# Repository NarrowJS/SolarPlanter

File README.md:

# SolarPlanter

A solar powered smart planter with built in soil moisture level monitoring.

## Key Features

- **ESP32-C3** microcontroller with WiFi + BLE Support
- **650 MAH** LiPo for backup power
- Built in **RGB LEDS** for notifications
- **Online logging** and monitoring via ESPHome
- **Motion sensor** to provide relevant notifications
- **ADC** to monitor battery voltage levels

## Why?

Keeping track of your plant's mositure, knowing when to water it, and also remembering to water it can be a challenging task, especially if you have more than one plant. Wanting a solution that was discrete and did not need me to ever charge the battery led me to make SolarPlanter.

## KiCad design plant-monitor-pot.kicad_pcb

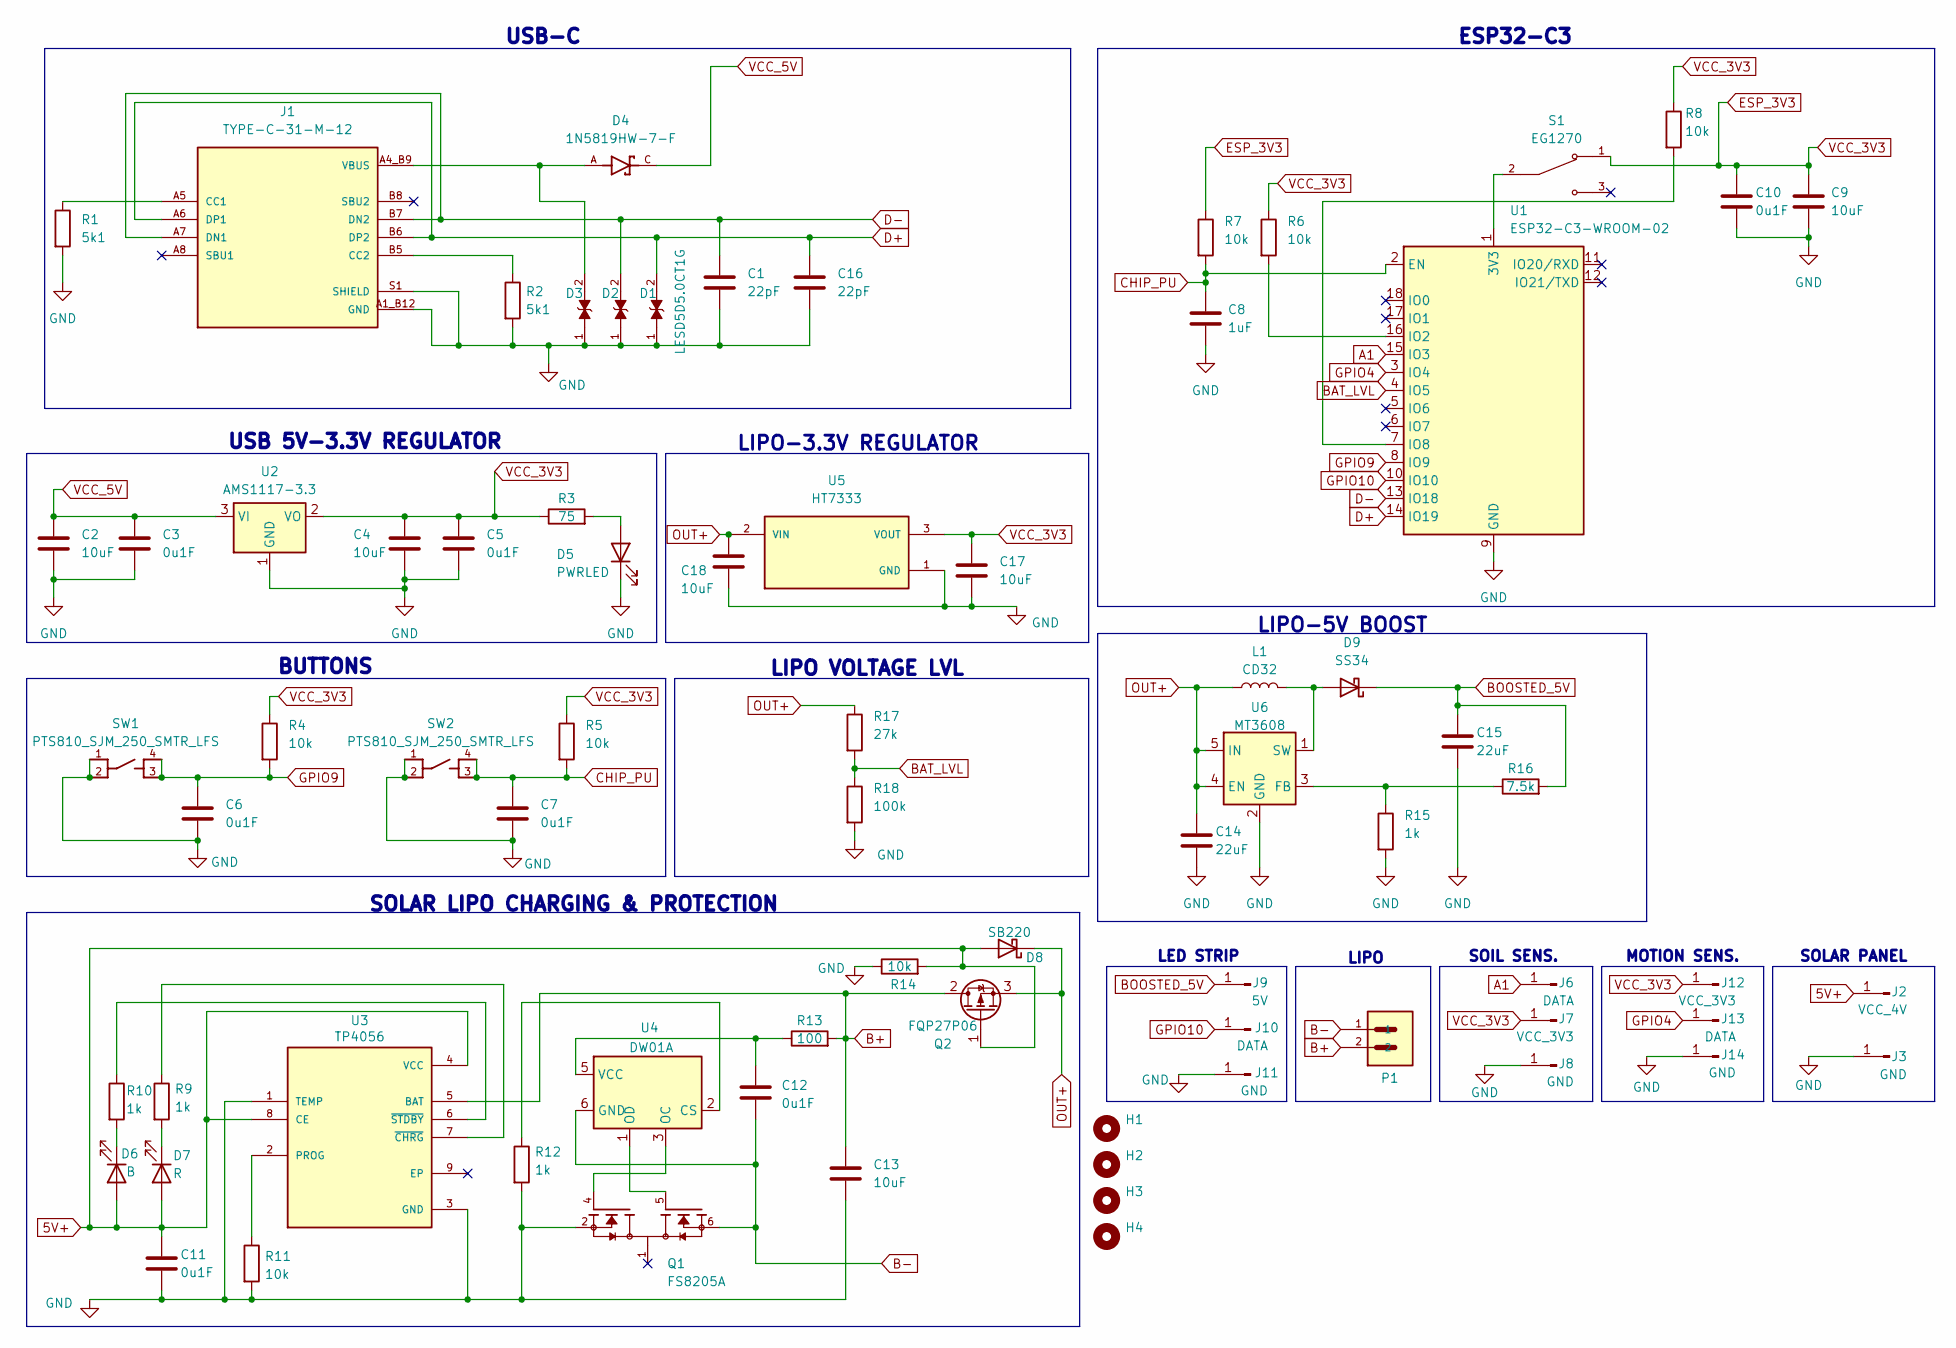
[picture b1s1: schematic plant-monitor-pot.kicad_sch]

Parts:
C1, C16: 22pF; C_0805_2012Metric
C2, C4, C9, C13, C17, C18: 10uF; C_0805_2012Metric
C3, C5, C6, C7, C10, C11, C12: 0u1F; C_0805_2012Metric
C8: 1uF; C_0805_2012Metric
C14, C15: 22uF; C_0805_2012Metric
D1, D2, D3: LESD5D5.0CT1G; TVS_LESD5D5.0CT1G; PARTREV O
D4: 1N5819HW-7-F; SOD3715X145N; PARTREV 18-2
D5: PWRLED; LED_0402_1005Metric
D6: B; LED_0402_1005Metric
D7: R; LED_0402_1005Metric
D8: SB220; D_0402_1005Metric
D9: SS34; D_SMA
H1, H2, H3, H4: MountingHole; MountingHole_2.2mm_M2
J1: TYPE-C-31-M-12; HRO_TYPE-C-31-M-12; PARTREV 2020.12.08
J2: VCC_4V; SolderWirePad_1x01_SMD_1x2mm
J3, J8, J11, J14: GND; SolderWirePad_1x01_SMD_1x2mm
J6, J10, J13: DATA; SolderWirePad_1x01_SMD_1x2mm
J7, J12: VCC_3V3; SolderWirePad_1x01_SMD_1x2mm
J9: 5V; SolderWirePad_1x01_SMD_1x2mm
L1: CD32; D_SMP_DO-220AA
P1: S2B-PH-SM4-TB; JST_S2B-PH-SM4-TB
Q1: FS8205A; SOP65P640X120-8N; PARTREV 1.7
Q2: FQP27P06; TO-220-3_Vertical
R1, R2: 5k1; R_0805_2012Metric
R3: 75; R_0805_2012Metric
R4, R5, R6, R7, R8, R11, R14: 10k; R_0805_2012Metric
R9, R10, R12, R15: 1k; R_0805_2012Metric
R13: 100; R_0805_2012Metric
R16: 7.5k; R_0805_2012Metric
R17: 27k; R_0805_2012Metric
R18: 100k; R_0805_2012Metric
S1: EG1270; SW_EG1270
SW1, SW2: PTS810_SJM_250_SMTR_LFS; SW_PTS810_SJM_250_SMTR_LFS
U1: ESP32-C3-WROOM-02
U2: AMS1117-3.3; SOT-223-3_TabPin2
U3: TP4056; SOP127P600X175-9N
U4: DW01A; SOT-23-6
U5: HT7333; IC_HT7333; PARTREV 1.80
U6: MT3608; SOT-23-6

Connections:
5V+: C11.1, D6.2 (A), D7.2 (A), D8.2 (A), J2.1, Q2.1 (G), R14.2, U3.4 (VCC), U3.8 (CE); also elsewhere on the board
A1: J6.1, U1.15 (IO3)
B+: C13.1, P1.2, Q2.2 (D), R13.2, U3.5 (BAT)
B-: C12.2, P1.1, Q1.6, Q1.7, U4.6 (GND)
BAT_LVL: R17.2, R18.1, U1.4 (IO5)
BOOSTED_5V: C15.1, D9.1 (K), J9.1, R16.2
CHIP_PU: C7.1, C8.1, R5.2, R7.2, SW2.3, SW2.4, U1.2 (EN)
D+: C16.1, D1.2, J1.A6 (DP1), J1.B6 (DP2), U1.14 (IO19)
D-: C1.1, D2.2, J1.A7 (DN1), J1.B7 (DN2), U1.13 (IO18)
ESP_3V3: C4.1, C5.1, C9.1, C10.1, C17.1, J7.1, J12.1, R3.1, R4.1, R5.1, R6.1, R7.1, R8.1, S1.1, U2.2 (VO), U5.3 (VOUT)
GND: C1.2, C2.2, C3.2, C4.2, C5.2, C6.2, C7.2, C8.2, C9.2, C10.2, C11.2, C13.2, C14.2, C15.2, C16.2, C17.2, C18.2, D1.1, D2.1, D3.1, D5.1 (K), J1.A1_B12 (GND), J1.B1_A12 (GND), J1.S1 (SHIELD), J1.S2 (SHIELD), J1.S3 (SHIELD), J1.S4 (SHIELD), J3.1, J8.1, J11.1, J14.1, Q1.2, Q1.3, R1.2, R2.2, R11.2, R12.2, R14.1, R15.2, R18.2, SW1.1, SW1.2, SW2.1, SW2.2, U1.9 (GND), U1.19 (GND), U2.1 (GND), U3.1 (TEMP), U3.3 (GND), U5.1 (GND), U6.2 (GND); also elsewhere on the board
GPIO4: J13.1, U1.3 (IO4)
GPIO9: C6.1, R4.2, SW1.3, SW1.4, U1.8 (IO9)
GPIO10: J10.1, U1.10 (IO10)
unnamed 14: D5.2 (A), R3.2; also elsewhere on the board
unnamed: D6.1 (K), R10.2
unnamed: D7.1 (K), R9.2
unnamed: D9.2 (A), L1.2, U6.1 (SW)
unnamed: J1.A5 (CC1), R1.1
unnamed: J1.B5 (CC2), R2.1
unnamed: S1.2, U1.1 (3V3)
unnamed: R6.2, U1.16 (IO2)
unnamed: R8.2, U1.7 (IO8)
unnamed: R11.1, U3.2 (PROG)
unnamed: R9.1, U3.7 (~CHRG)
unnamed: R10.1, U3.6 (~STDBY)
unnamed: R12.1, U4.2 (CS)
unnamed: Q1.4, U4.3 (OC)
unnamed: Q1.5, U4.1 (OD)
unnamed: C12.1, R13.1, U4.5 (VCC)
unnamed: R15.1, R16.1, U6.3 (FB)
OUT+: C14.1, C18.1, D8.1 (K), L1.1, Q2.3 (S), R17.1, U5.2 (VIN), U6.4 (EN), U6.5 (IN); also elsewhere on the board
VBUS: D3.2, D4.A, J1.A4_B9 (VBUS), J1.B4_A9 (VBUS)
VCC_5V: C2.1, C3.1, D4.C, U2.3 (VI)

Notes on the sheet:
BUTTONS
SOLAR PANEL
LIPO
SOIL SENS.
LED STRIP
ESP32-C3
USB-C
MOTION SENS.
USB 5V-3.3V REGULATOR
LIPO-5V BOOST
SOLAR LIPO CHARGING & PROTECTION
LIPO VOLTAGE LVL
LIPO-3.3V REGULATOR

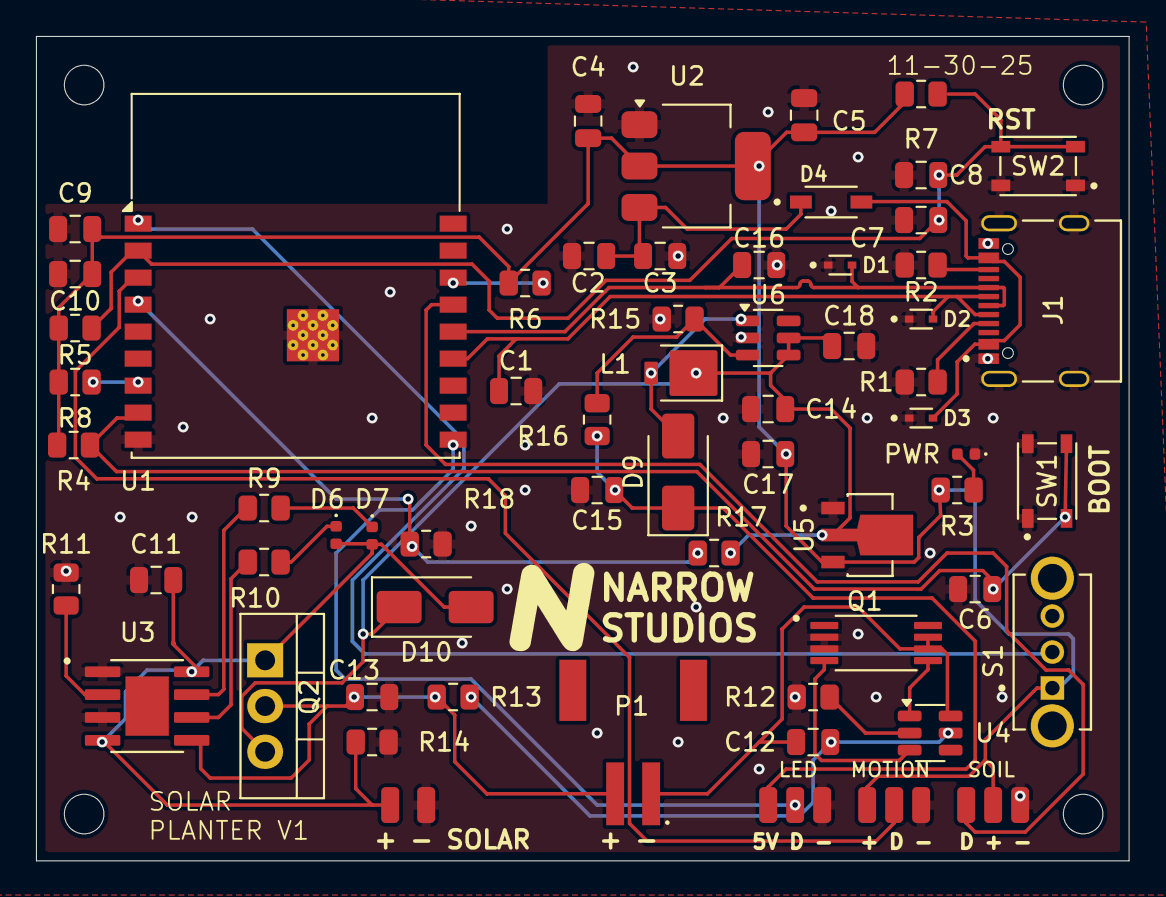
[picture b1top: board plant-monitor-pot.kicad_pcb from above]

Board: 2 copper layers, 60.7 x 45.8 mm, 75 parts (0 on the bottom side), 34 nets.

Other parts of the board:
D10: SS24; D_SMA
PWR: PWRLED; LED_0402_1005Metric
e: LOGO; ns-logo

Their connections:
5V+: D10.2 (A); also elsewhere on the board
GND: PWR.1 (K); also elsewhere on the board
unnamed 14: PWR.2 (A); also elsewhere on the board
OUT+: D10.1 (K); also elsewhere on the board

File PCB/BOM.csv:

"Id";"Designator";"Footprint";"Quantity";"Designation";"Supplier and ref";
1;"R9,R15,R10,R12";"R_0805_2012Metric";4;"1k";;;
2;"J3,J14,J8,J11";"SolderWirePad_1x01_SMD_1x2mm";4;"GND";;;
3;"J7,J12";"SolderWirePad_1x01_SMD_1x2mm";2;"VCC_3V3";;;
4;"R1,R2";"R_0805_2012Metric";2;"5k1";;;
5;"L1";"D_SMP_DO-220AA";1;"CD32";;;
6;"U2";"SOT-223-3_TabPin2";1;"AMS1117-3.3";;;
7;"U6";"SOT-23-6";1;"MT3608";;;
8;"D4";"SOD3715X145N";1;"1N5819HW-7-F";;;
9;"C18,C17,C13,C4,C2,C9";"C_0805_2012Metric";6;"10uF";;;
10;"J10,J6,J13";"SolderWirePad_1x01_SMD_1x2mm";3;"DATA";;;
11;"S1";"SW_EG1270";1;"EG1270";;;
12;"P1";"JST_S2B-PH-SM4-TB";1;"S2B-PH-SM4-TB";;;
13;"R3";"R_0805_2012Metric";1;"75";;;
14;"Q2";"TO-220-3_Vertical";1;"FQP27P06";;;
15;"J1";"HRO_TYPE-C-31-M-12";1;"TYPE-C-31-M-12";;;
16;"R11,R6,R7,R5,R8,R4,R14";"R_0805_2012Metric";7;"10k";;;
17;"SW2,SW1";"SW_PTS810_SJM_250_SMTR_LFS";2;"PTS810_SJM_250_SMTR_LFS";;;
18;"C15,C14";"C_0805_2012Metric";2;"22uF";;;
19;"C10,C7,C3,C5,C11,C12,C6";"C_0805_2012Metric";7;"0u1F";;;
20;"U4";"SOT-23-6";1;"DW01A";;;
21;"C16,C1";"C_0805_2012Metric";2;"22pF";;;
22;"U1";"ESP32-C3-WROOM-02";1;"ESP32-C3-WROOM-02";;;
23;"R18";"R_0805_2012Metric";1;"100k";;;
24;"R17";"R_0805_2012Metric";1;"27k";;;
25;"D6";"LED_0402_1005Metric";1;"B";;;
26;"R16";"R_0805_2012Metric";1;"7.5k";;;
27;"J9";"SolderWirePad_1x01_SMD_1x2mm";1;"5V";;;
28;"D8";"D_0402_1005Metric";1;"SB220";;;
29;"Q1";"SOP65P640X120-8N";1;"FS8205A";;;
30;"D7";"LED_0402_1005Metric";1;"R";;;
31;"U3";"SOP127P600X175-9N";1;"TP4056";;;
32;"C8";"C_0805_2012Metric";1;"1uF";;;
33;"D9";"D_SMA";1;"SS34";;;
34;"D2,D3,D1";"TVS_LESD5D5.0CT1G";3;"LESD5D5.0CT1G";;;
35;"U5";"IC_HT7333";1;"HT7333";;;
36;"R13";"R_0805_2012Metric";1;"100";;;
37;"J2";"SolderWirePad_1x01_SMD_1x2mm";1;"VCC_4V";;;
38;"PWR";"LED_0402_1005Metric";1;"PWRLED";;;

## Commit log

2025-12-06 readme
2025-12-07 pcb v2
    changed pcb, photo, and upload new bom
2025-12-07 Revert "pcb v2"
2025-12-07 new pcb
2025-12-07 changed the pcb and bom
2025-12-07 updated main parts BOM
2025-12-07 changed bom to not duplicate
2025-12-07 removed both boms
2025-12-07 added back bom
2025-12-07 updated bom layout
2025-12-07 updated bom v2
2025-12-07 added pcb render
